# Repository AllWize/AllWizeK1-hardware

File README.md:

# AllWize K1

The Allwize K1 shield is an Arduino-compatible shield based on the RadioCrafts RC1701HP module. 

Resources:

* [AllWize K1 Wiki Page](http://wiki.allwize.io/index.php?title=Allwize_K1)
* [AllWize Library](https://github.com/AllWize/allwize) that supports the RC1701HP radio module.

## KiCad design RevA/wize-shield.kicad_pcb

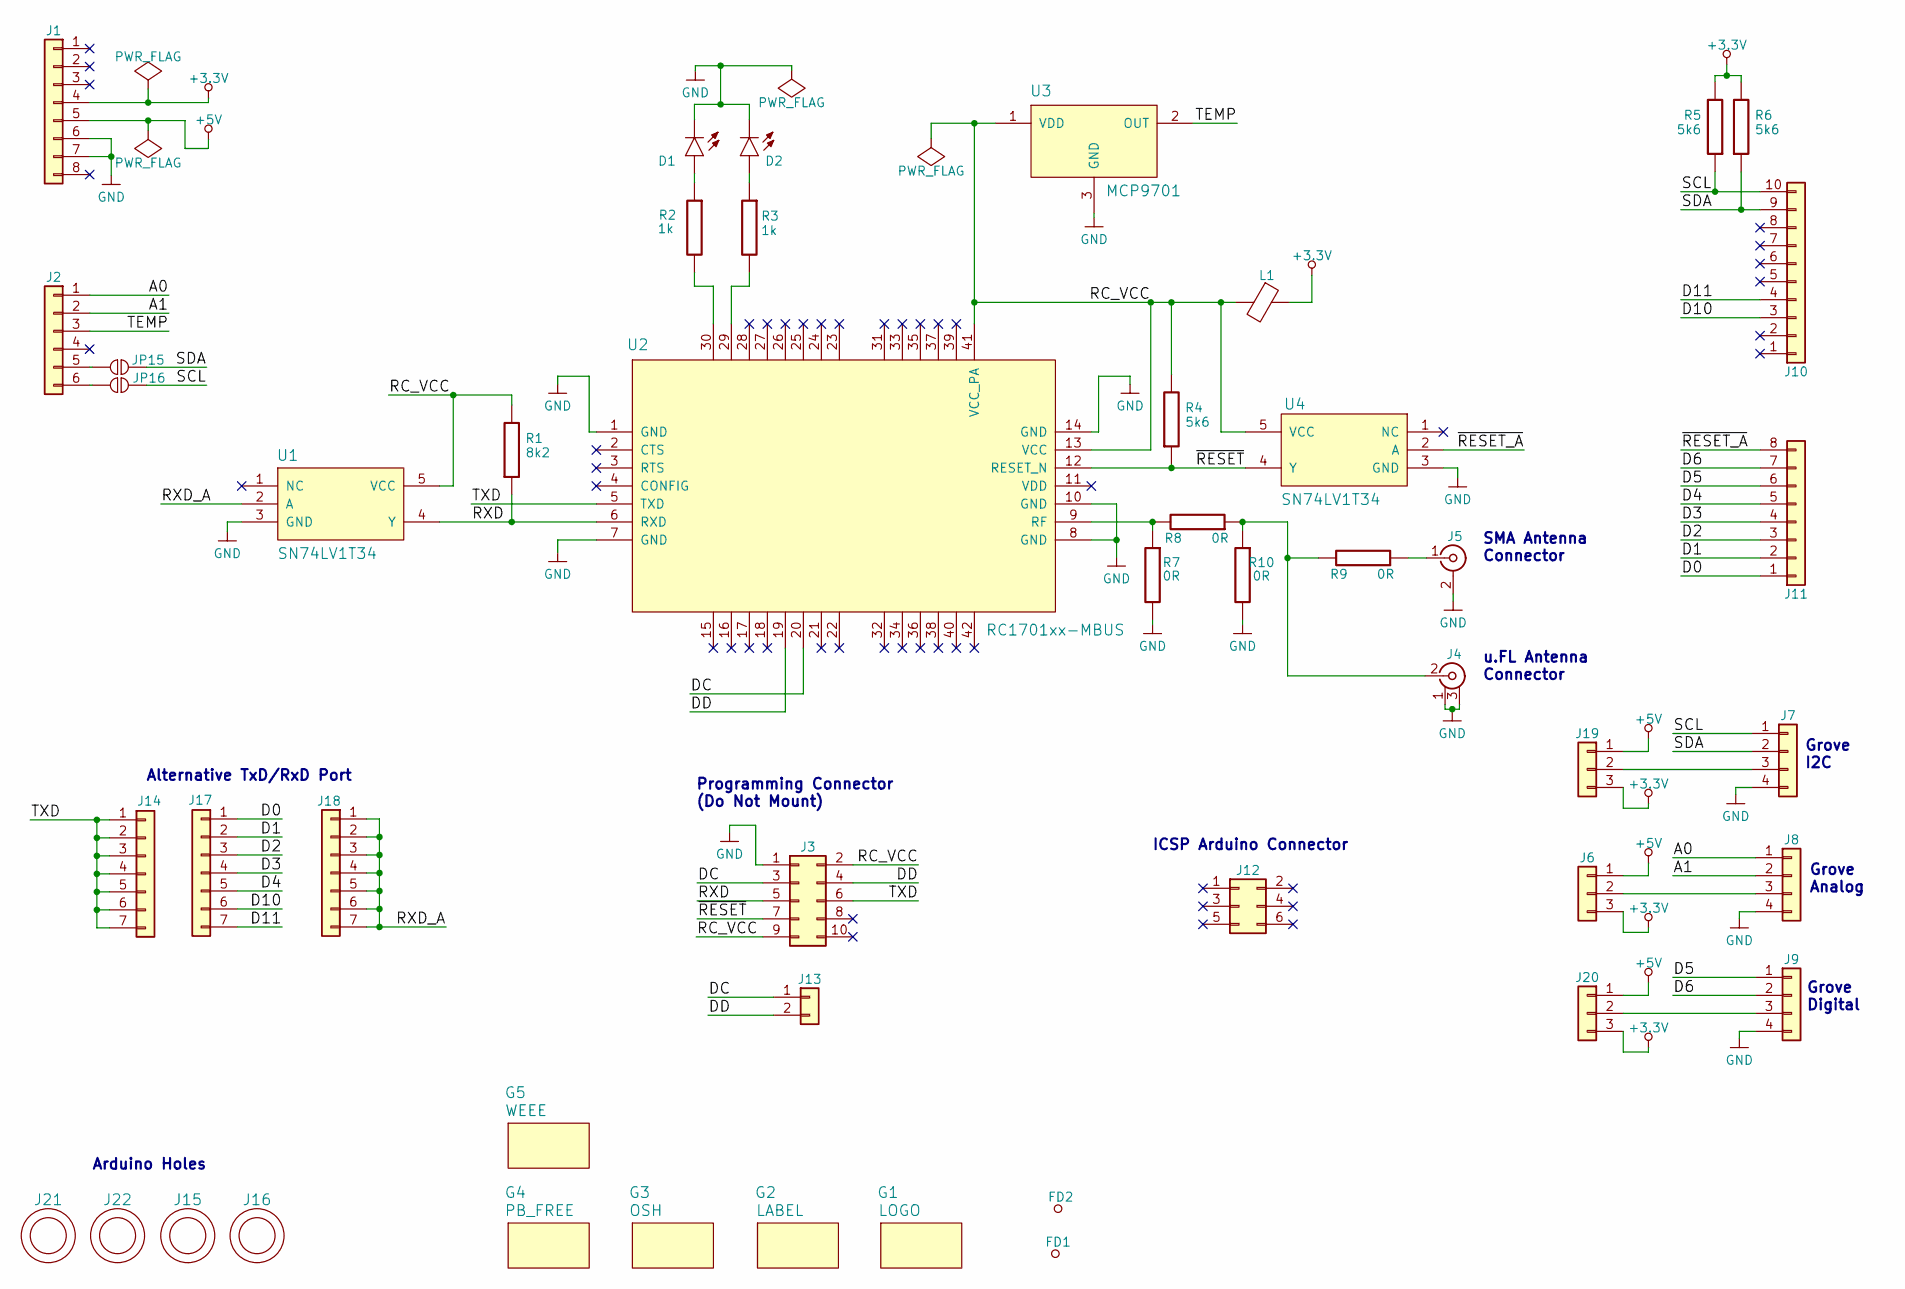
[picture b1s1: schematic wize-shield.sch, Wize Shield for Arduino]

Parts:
D1, D2: LED-DIODE; LED_0603
FD1, FD2: FIDUCIAL; FIDUCIAL-08
G1: LOGO; allwize-logo-2
G2: LABEL; LABEL_15x7mm
G3: OSH; osh
G4: PB_FREE; Pb-free
G5: WEEE
J1, J11: Conn_01x08; PinHeader_1x08_P2.54mm_Vertical
J2: Conn_01x06; PinHeader_1x06_P2.54mm_Vertical
J3: Conn_02x05_Odd_Even; PinHeader_2x05_P1.27mm_Vertical_SMD
J4: Conn_Coaxial_uFL; uFL-CONN
J5: Conn_Coaxial; SMA_Jack
J6, J19, J20: Conn_01x03; PinHeader_1x03_P2.54mm_Vertical
J7, J8, J9: Conn_01x04; GROVE-TH-1x04-P2.00mm_Horizontal
J10: Conn_01x10; PinHeader_1x10_P2.54mm_Vertical
J12: Conn_02x03_Odd_Even; PinHeader_2x03_P2.54mm_Vertical
J13: Conn_01x02; PinHeader_1x02_P2.54mm_Vertical
J14, J17, J18: Conn_01x07; PinHeader_1x07_P2.54mm_Vertical
J15, J16, J21, J22: NPTH-HOLE; HOLE_3.10MM
JP15, JP16: SolderJumper_2_Open; SolderJumper-2_P1.3mm_Open_Pad1.0x1.5mm
L1: Ferrite_Bead; R_0603
R1: 8k2; R_0603
R2, R3: 1k; R_0603
R4, R5, R6: 5k6; R_0603
R7, R8, R10: 0R; R_0603
R9: 0R; R_0603_ANTENNA
U1, U4: SN74LV1T34; SOT-23-5
U2: RC1701xx-MBUS
U3: MCP9701; SOT-23-3

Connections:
+3.3V: J1.4, J6.3, J19.3, J20.3, L1.1, R5.2, R6.2
+5V: J1.5, J6.1, J19.1, J20.1
/A0: J2.1, J8.1
/A1: J2.2, J8.2
/D0: J11.1, J17.1
/D1: J11.2, J17.2
/D2: J11.3, J17.3
/D3: J11.4, J17.4
/D4: J11.5, J17.5
/D5: J9.1, J11.6
/D6: J9.2, J11.7
/D10: J10.3, J17.6
/D11: J10.4, J17.7
/DC: J3.3, J13.1, U2.20
/DD: J3.4, J13.2, U2.19
/RC_VCC: J3.2, J3.9, L1.2, R1.2, R4.2, U1.5 (VCC), U2.13 (VCC), U2.41 (VCC_PA), U3.1 (VDD), U4.5 (VCC)
/RXD: J3.5, R1.1, U1.4 (Y), U2.6 (RXD)
/RXD_A: J18.1, J18.2, J18.3, J18.4, J18.5, J18.6, J18.7, U1.2 (A)
/SCL: J7.1, J10.10, JP16.2 (B), R5.1
/SDA: J7.2, J10.9, JP15.2 (B), R6.1
/TEMP: J2.3, U3.2 (OUT)
/TXD: J3.6, J14.1, J14.2, J14.3, J14.4, J14.5, J14.6, J14.7, U2.5 (TXD)
/~RESET_A~: J11.8, U4.2 (A)
/~RESET~: J3.7, R4.1, U2.12 (RESET_N), U4.4 (Y)
GND: D1.2 (C), D2.2 (C), J1.6, J1.7, J3.1, J4.1 (Ext), J4.3 (Ext), J5.2 (Ext), J7.4, J8.4, J9.4, R7.2, R10.2, U1.3 (GND), U2.1 (GND), U2.7 (GND), U2.8 (GND), U2.10 (GND), U2.14 (GND), U3.3 (GND), U4.3 (GND)
unnamed: D1.1 (A), R2.1
unnamed: D2.1 (A), R3.1
unnamed: J2.5, JP15.1 (A)
unnamed: J2.6, JP16.1 (A)
unnamed: J4.2 (In), R8.1, R9.2, R10.1
unnamed: J5.1 (In), R9.1
unnamed: J6.2, J8.3
unnamed: J7.3, J19.2
unnamed: J9.3, J20.2
unnamed: R2.2, U2.30
unnamed: R3.2, U2.29
unnamed: R7.1, R8.2, U2.9 (RF)

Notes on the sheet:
Programming Connector (Do Not Mount)
Alternative TxD/RxD Port
Grove I2C
Grove Analog
Grove Digital
ICSP Arduino Connector
Arduino Holes
SMA Antenna Connector
u.FL Antenna Connector

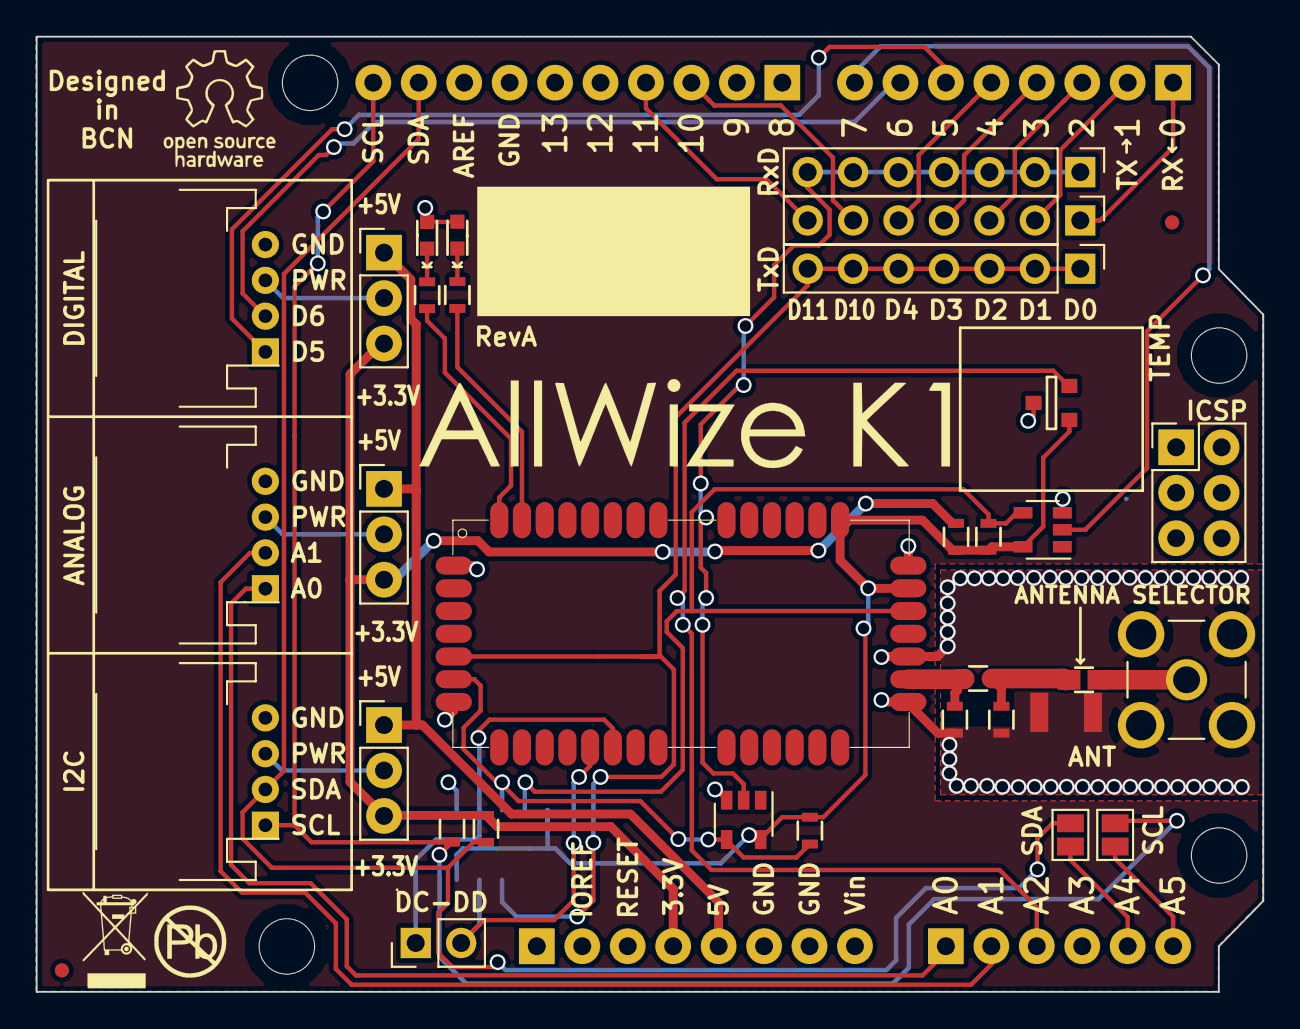
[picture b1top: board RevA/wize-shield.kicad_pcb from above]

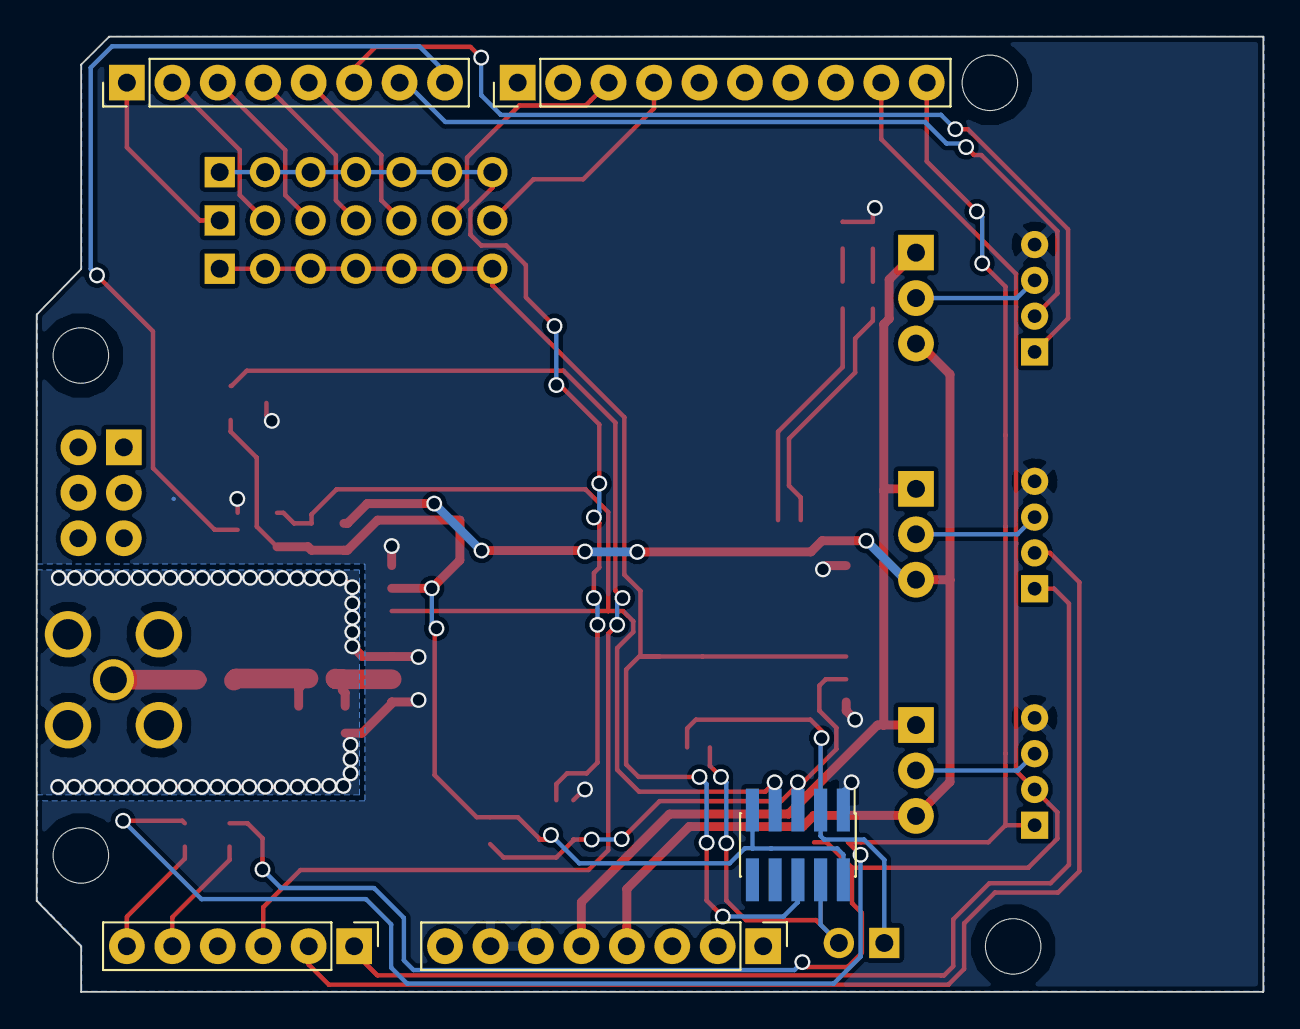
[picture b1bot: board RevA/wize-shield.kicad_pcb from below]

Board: 2 copper layers, 68.5 x 53.4 mm, 48 parts (5 on the bottom side), 37 nets.

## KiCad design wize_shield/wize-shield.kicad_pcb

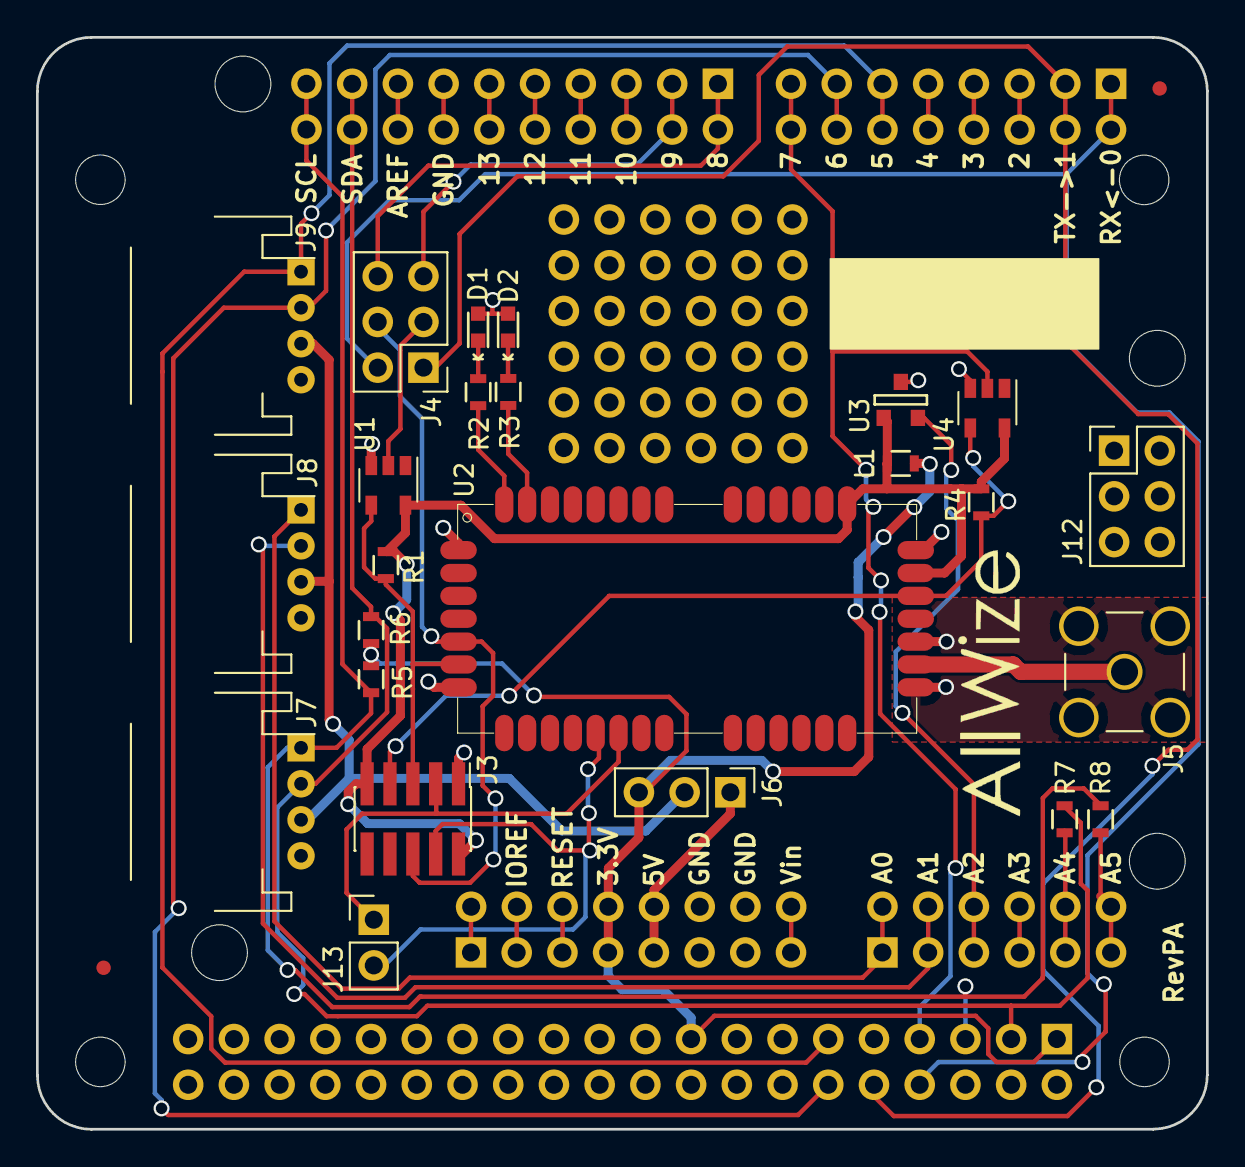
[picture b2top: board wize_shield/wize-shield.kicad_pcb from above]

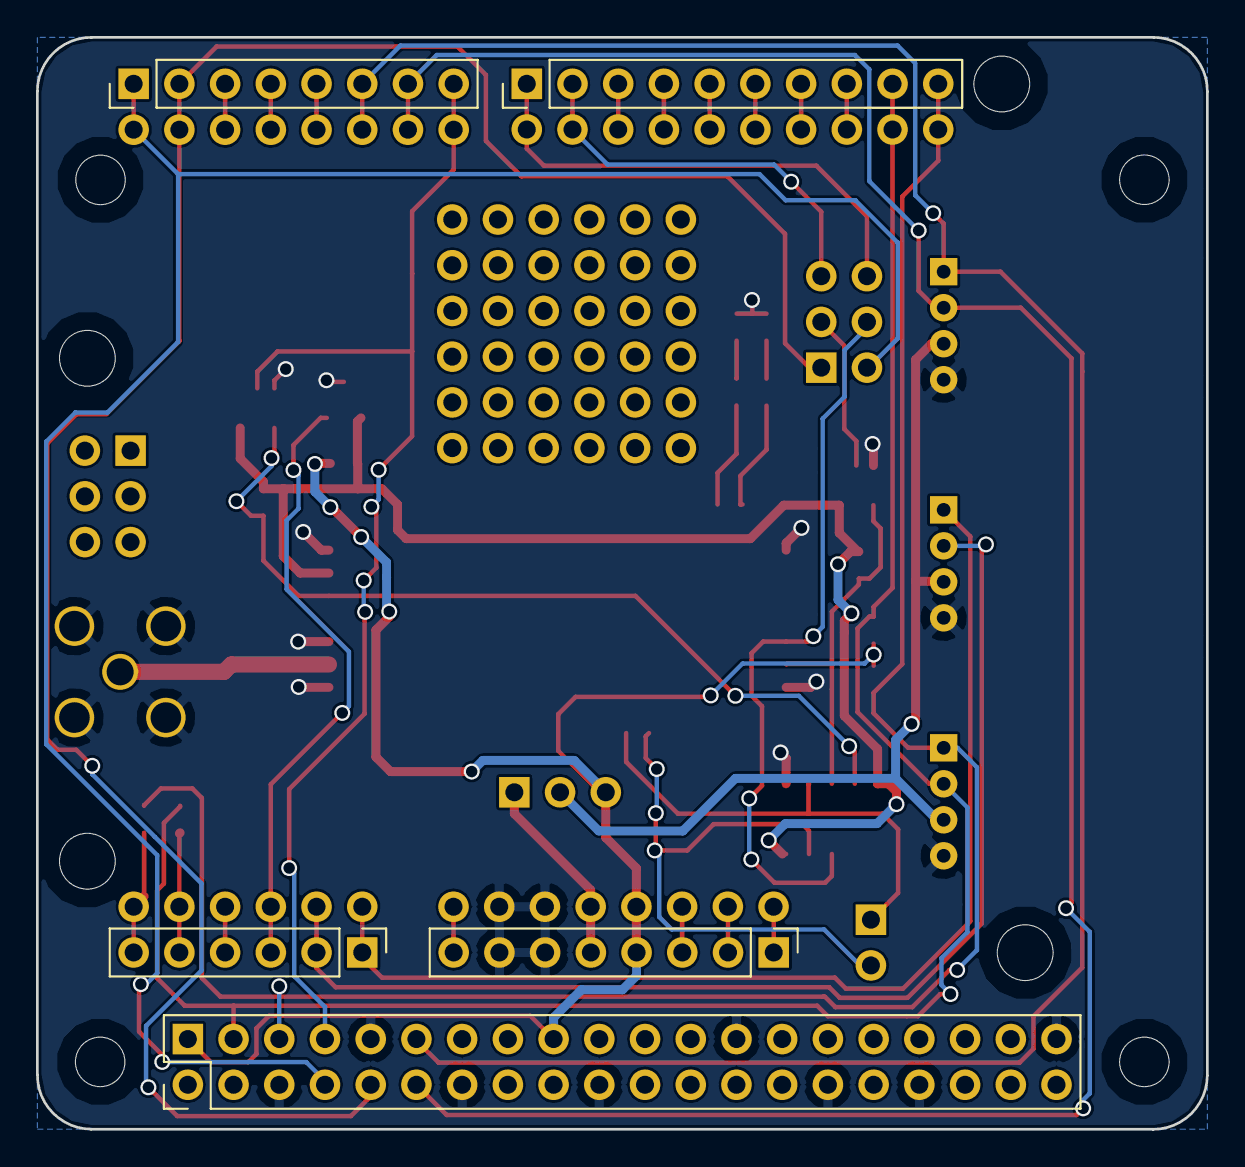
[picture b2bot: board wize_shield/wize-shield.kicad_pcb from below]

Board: 2 copper layers, 65.0 x 60.7 mm, 46 parts (5 on the bottom side), 44 nets.

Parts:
D1, D2: LED-DIODE; LED_0603
FD1, FD2: FIDUCIAL; FIDUCIAL-08
G1: LOGO; allwize-logo-2
G2: LABEL; LABEL_15x5mm
G3: PROTOTYPE-AREA; Prototype-Area_06x06_P2.54mm
J1, J11: Conn_01x08; PinHeader_1x08_P2.54mm_Vertical
J2: Conn_01x06; PinHeader_1x06_P2.54mm_Vertical
J3: Conn_02x05_Odd_Even; PinHeader_2x05_P1.27mm_Vertical_SMD
J4, J12: Conn_02x03_Odd_Even; PinHeader_2x03_P2.54mm_Vertical
J5: Conn_Coaxial; SMA_Jack
J6: Conn_01x03; PinHeader_1x03_P2.54mm_Vertical
J7, J8, J9: Conn_01x04; GROVE-TH-1x04-P2.00mm_Horizontal
J10: Conn_01x10; PinHeader_1x10_P2.54mm_Vertical
J13: Conn_01x02; PinHeader_1x02_P2.54mm_Vertical
J14: Conn_02x20_Odd_Even; PinHeader_2x20_P2.54mm_Vertical_Pin1_Right
J15, J16, J21, J22: NPTH-HOLE; HOLE_3.10MM
J17, J18, J19, J20: NPTH-HOLE; HOLE_2.75MM
J23, J26: Conn_01x08; PAD_1x08_P2.54mm
J24: Conn_01x06; PAD_1x06_P2.54mm
J25: Conn_01x10; PAD_1x010_P2.54mm
L1: Ferrite_Bead; R_0603
R1: 8k2; R_0603
R2, R3: 1k; R_0603
R4, R5, R6: 5k6; R_0603
R7, R8: 0R; R_0603
U1, U4: SN74LV1T34; SOT-23-5
U2: RC1701xx-MBUS
U3: MCP9701; SOT-23-3

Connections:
+3.3V: J1.4, J6.3, J14.1, J14.17, J23.4, L1.1, R5.2, R6.2
+5V: J1.5, J6.1, J23.5
/5V-3.3V: J6.2, J7.3, J8.3, J9.3
/A0: J2.1, J8.1, J24.1
/A1: J2.2, J8.2, J24.2
/D6: J9.1, J11.6, J14.11, J26.6
/D7: J9.2, J11.7, J14.12, J26.7
/DC: J3.3, J13.1, U2.20
/DD: J3.4, J13.2, U2.19
/RC_VCC: J3.2, J3.9, L1.2, R1.2, R4.2, U1.5, U2.13, U2.41, U3.1, U4.5
/RXD: J3.5, R1.1, U1.4, U2.6
/RXD_A: J4.3, U1.2
/RXD_A1: J4.1, J11.2, J14.10, J26.2
/RXD_A2: J4.5, J10.2, J25.2
/SCL: J7.1, J10.10, J14.5, J25.10, R5.1, R8.1
/SDA: J7.2, J10.9, J14.3, J25.9, R6.1, R7.1
/TEMP: J2.3, J24.3, U3.2
/TXD: J3.6, J4.4, U2.5
/TXD_A1: J4.2, J11.1, J14.8, J26.1
/TXD_A2: J4.6, J10.1, J25.1
/~RESET_A~: J11.8, J14.7, J26.8, U4.2
/~RESET~: J3.7, R4.1, U2.12, U4.4
GND: D1.2, D2.2, J1.6, J1.7, J3.1, J5.2, J7.4, J8.4, J9.4, J14.6, J14.9, J14.14, J14.20, J14.25, J14.30, J14.34, J14.39, J23.6, J23.7, U1.3, U2.1, U2.7, U2.8, U2.10, U2.14, U3.3, U4.3
unnamed: D1.1, R2.1
unnamed: D2.1, R3.1
unnamed: J1.1, J23.1
unnamed: J1.2, J23.2
unnamed: J1.3, J23.3
unnamed: J1.8, J23.8
unnamed: J2.4, J24.4
unnamed: J2.5, J24.5, R7.2
unnamed: J2.6, J24.6, R8.2
unnamed: J5.1, U2.9
unnamed: J10.3, J25.3
unnamed: J10.4, J25.4
unnamed: J10.5, J25.5
unnamed: J10.6, J25.6
unnamed: J10.7, J25.7
unnamed: J10.8, J25.8
unnamed: J11.3, J26.3
unnamed: J11.4, J26.4
unnamed: J11.5, J26.5
unnamed: R2.2, U2.30
unnamed: R3.2, U2.29

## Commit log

2018-04-17 Adding Wize Shield, RevPA
    Prototype A version, made by Gaston Schelotto
2018-08-23 Reorganisation
    Reorganisation of the folder to separate between versions PA and PB
2019-08-21 Add links to the wiki in the README page
2019-08-26 Adding K1-RevA
2019-08-26 Adding the laser-cutting enclosure files
